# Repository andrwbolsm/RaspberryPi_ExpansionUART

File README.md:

## Context
 
The Raspberry Pi exposes only one hardware UART, which is insufficient when simultaneous communication with multiple devices is required. In this project, each drone in a six-drone swarm uses a dedicated 433 MHz radio transceiver connected over UART. To handle six transceivers from a single Raspberry Pi, a custom expansion board (HAT) was designed using the SC16IS752, natively supported by Linux.
 
A key motivation for moving away from USB was power delivery: the Raspberry Pi's USB ports do not supply enough current to reliably drive multiple radio modules, even through powered hubs. Bypassing USB in favour of direct UART with battery-sourced power resolves this limitation.
 
---
 
## System Architecture
 
```
[ Battery ]
     │
     ├──► [ Voltage Regulator (5V) ] ──► [ SC16IS752 ]
     │                                        │
[ Raspberry Pi ]                       UART A (/dev/ttySC0) ──► Radio transceiver 1
  I²C bus ──────────────────────────►  UART B (/dev/ttySC1) ──► Radio transceiver 2
                                        (stack additional chips for more channels)
```
 
- Power for the SC16IS752 is drawn **directly from the battery** through a regulator, bypassing the Raspberry Pi's USB current limit.
- The I²C bus from the Raspberry Pi controls the chip; Linux automatically exposes each UART as `/dev/ttySC0` and `/dev/ttySC1`.
- Multiple chips can be stacked on the same I²C bus using different A0/A1 addresses, scaling up to 32 UART channels.
 
---
 
## Hardware
 
| Component | Role |
|---|---|
| Raspberry Pi | Main onboard computer (Linux) |
| SC16IS752 | I²C-to-dual-UART bridge chip (2 ch UART + 8 GPIO) |
| 433 MHz radio transceivers | Long-range communication with drones (~400 m through buildings) |
| Voltage regulator | Supplies 5V (≥ 1W) to the chip from the battery |
| Custom HAT PCB | Designed with KiCad; connects directly to the Raspberry Pi GPIO header |
 
The radio modules operate in the **433 MHz band**, each assigned a separate channel to avoid inter-drone interference.
 
---
 
## Repository Structure
 
```
.
├── Code/               # Firmware / communication validation code (C)
├── Projet_Tschema/     # PCB schematic and layout files (KiCad)
└── README.md
```
 
---
 
## Setup
 
### 1. Enable I²C on the Raspberry Pi
 
```bash
sudo raspi-config
# Navigate to: Interfacing Options → I2C → Yes
```
 
### 2. Register the SC16IS752 kernel driver
 
Append to `/boot/config.txt`:
 
```
dtoverlay=sc16is752-i2c,int_pin=24,addr=0x48
# addr changes according to A0/A1 jumper setting — default is 0x48
```
 
Then reboot:
 
```bash
sudo reboot
```
 
### 3. Verify UART devices are exposed
 
```bash
ls /dev/ttySC*
# Expected: /dev/ttySC0  /dev/ttySC1
```
 
---
 
## PCB Design
 
The expansion board is designed in **KiCad** (files in `Projet_Tschema/`). It plugs onto the Raspberry Pi GPIO header and provides:
 
- I²C connection to the SC16IS752
- Battery-sourced regulated 5V power rail for the chip
- UART connectors for each radio transceiver
   
---
 
## Software
 
The firmware (`Code/`, C) handles:
 
1. **UART validation** — confirms Linux correctly enumerates `/dev/ttySC0` and `/dev/ttySC1` after the HAT is mounted.
2. **Communication protocol** — data exchange with each radio transceiver over its dedicated UART channel.
 
---

## Validation Steps
 
1. Mount the HAT and power the SC16IS752 from the battery rail.
2. Confirm UART devices appear: `ls /dev/ttySC*`
3. Run the communication test to validate send/receive on one channel.
 
---
 
## Status
 
> Active development — PCB validation and multi-channel firmware in progress.

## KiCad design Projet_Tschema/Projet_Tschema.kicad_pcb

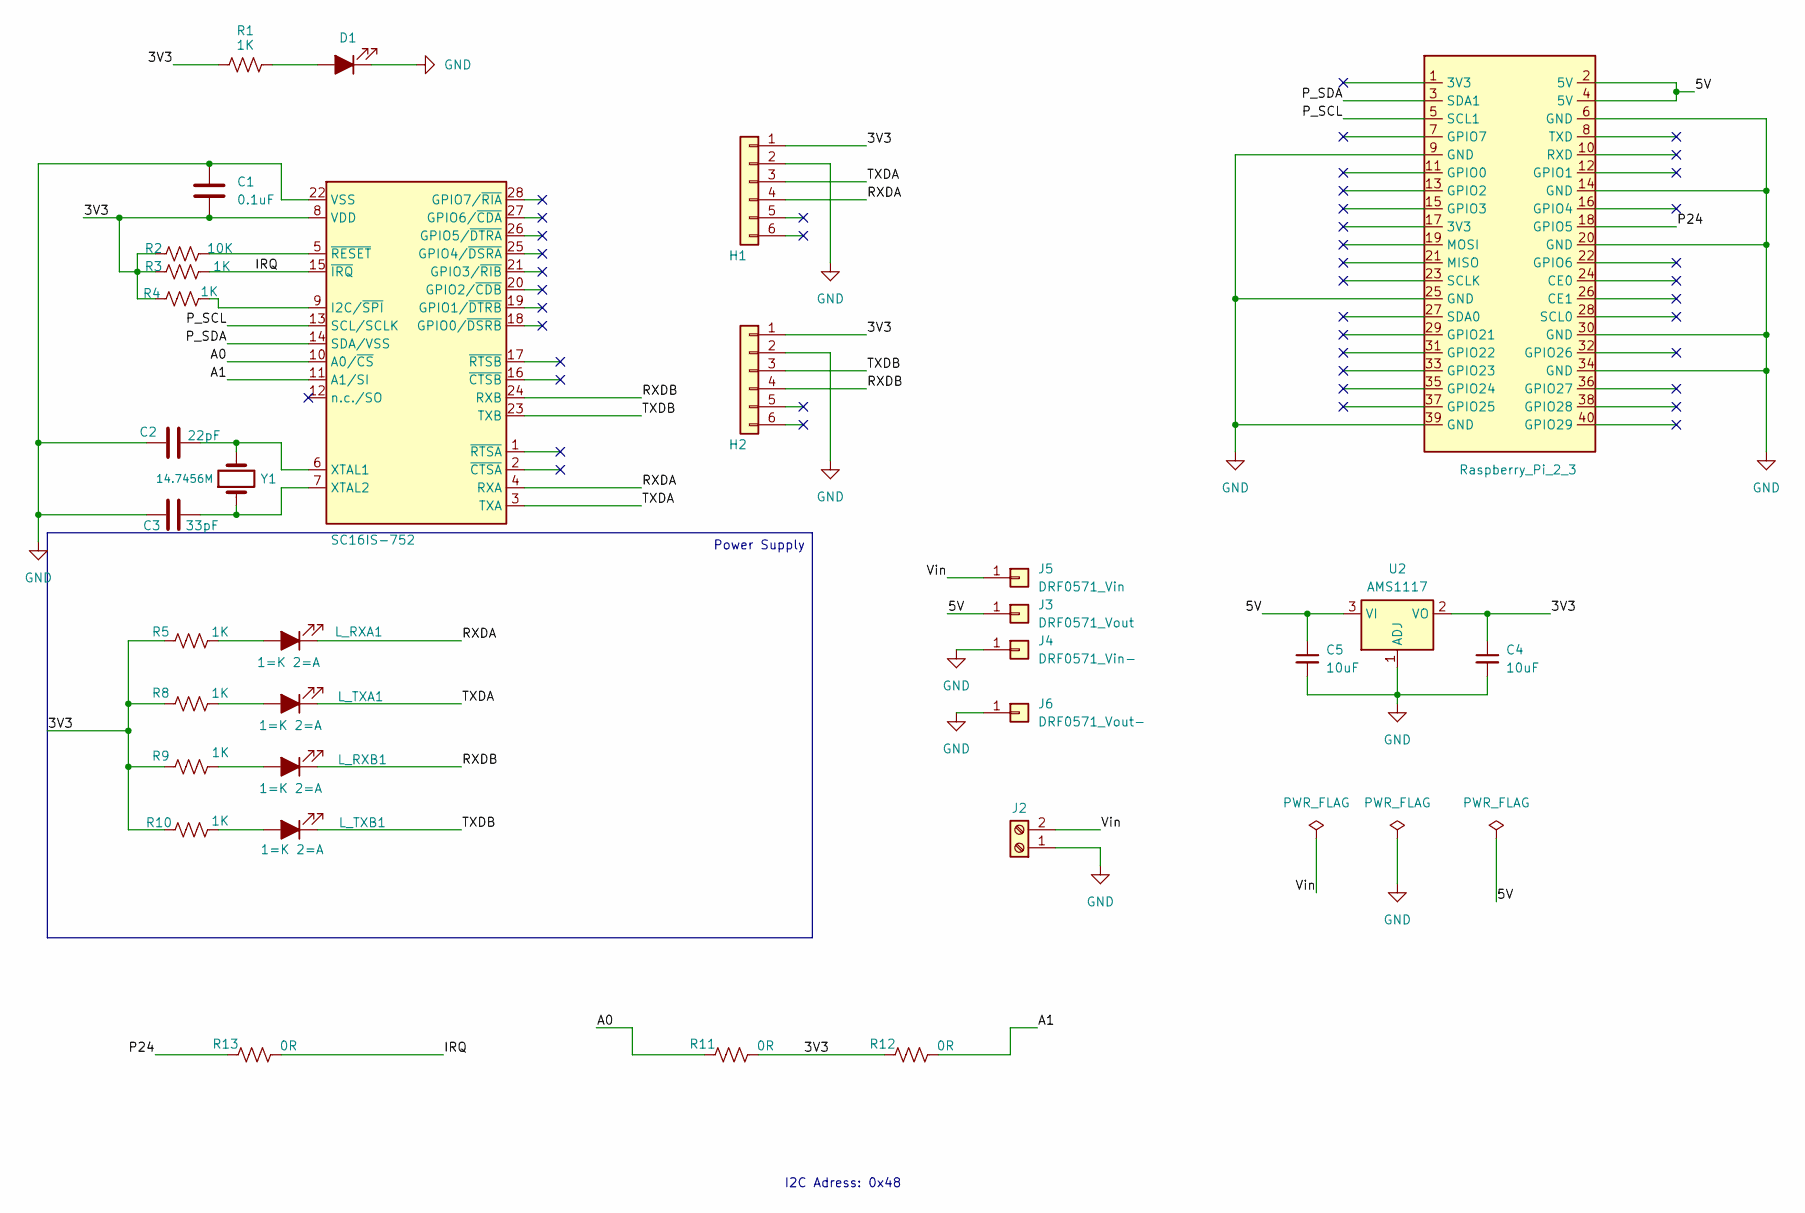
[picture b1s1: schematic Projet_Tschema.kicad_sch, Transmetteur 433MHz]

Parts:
C1: 0.1uF; C_0805_2012Metric
C2: 22pF; C_0805_2012Metric
C3: 33pF; C_0805_2012Metric
C4, C5: 10uF; C_0805_2012Metric
D1: LED_Filled; LED_0805_2012Metric
H1, H2: Conn_01x06; JST_GH_SM06B-GHS-TB_1x06-1MP_P1.25mm_Horizontal
J1: Raspberry_Pi_2_3; PinHeader_2x20_P2.54mm_Vertical
J2: Screw_Terminal_01x02; PinHeader_1x02_P2.54mm_Vertical
J3: DRF0571_Vout; PinHeader_1x01_P2.54mm_Vertical
J4: DRF0571_Vin-; PinHeader_1x01_P2.54mm_Vertical
J5: DRF0571_Vin; PinHeader_1x01_P2.54mm_Vertical
J6: DRF0571_Vout-; PinHeader_1x01_P2.54mm_Vertical
L_RXA1: LED_Filled; R_0805_2012Metric
L_RXB1: LED_Filled; R_0805_2012Metric
L_TXA1: LED_Filled; R_0805_2012Metric
L_TXB1: LED_Filled; R_0805_2012Metric
R1, R3, R4, R5, R8, R9, R10: 1K; R_0805_2012Metric
R2: 10K; R_0805_2012Metric
R11, R12, R13: 0R; R_0805_2012Metric
U1: SC16IS-752; TSSOP-28_4.4x9.7mm_P0.65mm
U2: AMS1117; SOT-223-3_TabPin2
Y1: 14.7456M; Crystal_HC52-U_Vertical

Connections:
/3V3: C1.2, C4.1, H1.1, H2.1, R1.1, R2.1, R3.1, R4.1, R5.1, R8.1, R9.1, R10.1, R11.2, R12.1, U1.8 (VDD), U2.2 (VO)
/5V: C5.1, J1.2 (5V), J1.4 (5V), J3.1, U2.3 (VI)
/&lt;NO NET&gt;: J1.27 (SDA0)
/A0: R11.1, U1.10 (A0/~CS)
/A1: R12.2, U1.11 (A1/SI)
/IRQ: R3.2, R13.2, U1.15 (~IRQ)
/P24: J1.18 (GPIO5), R13.1
/P_SCL: J1.5 (SCL1), U1.13 (SCL/SCLK)
/P_SDA: J1.3 (SDA1), U1.14 (SDA/VSS)
/RXDA: H1.4, L_RXA1.1 (K), U1.4 (RXA)
/RXDB: H2.4, L_RXB1.1 (K), U1.24 (RXB)
/TXDA: H1.3, L_TXA1.1 (K), U1.3 (TXA)
/TXDB: H2.3, L_TXB1.1 (K), U1.23 (TXB)
/Vin: J2.2, J5.1
GND: C1.1, C2.2, C3.2, C4.2, C5.2, D1.1 (K), H1.2, H2.2, J1.6 (GND), J1.9 (GND), J1.14 (GND), J1.20 (GND), J1.25 (GND), J1.30 (GND), J1.34 (GND), J1.39 (GND), J2.1, J4.1, J6.1, U1.22 (VSS), U2.1 (ADJ)
unnamed: D1.2 (A), R1.2
unnamed: L_RXA1.2 (A), R5.2
unnamed: L_RXB1.2 (A), R9.2
unnamed: L_TXA1.2 (A), R8.2
unnamed: L_TXB1.2 (A), R10.2
unnamed: R4.2, U1.9 (I2C/~SPI)
unnamed: C2.1, U1.6 (XTAL1), Y1.2
unnamed: C3.1, U1.7 (XTAL2), Y1.1
unnamed: R2.2, U1.5 (~RESET)

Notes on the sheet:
I2C Adress: 0x48
Power Supply

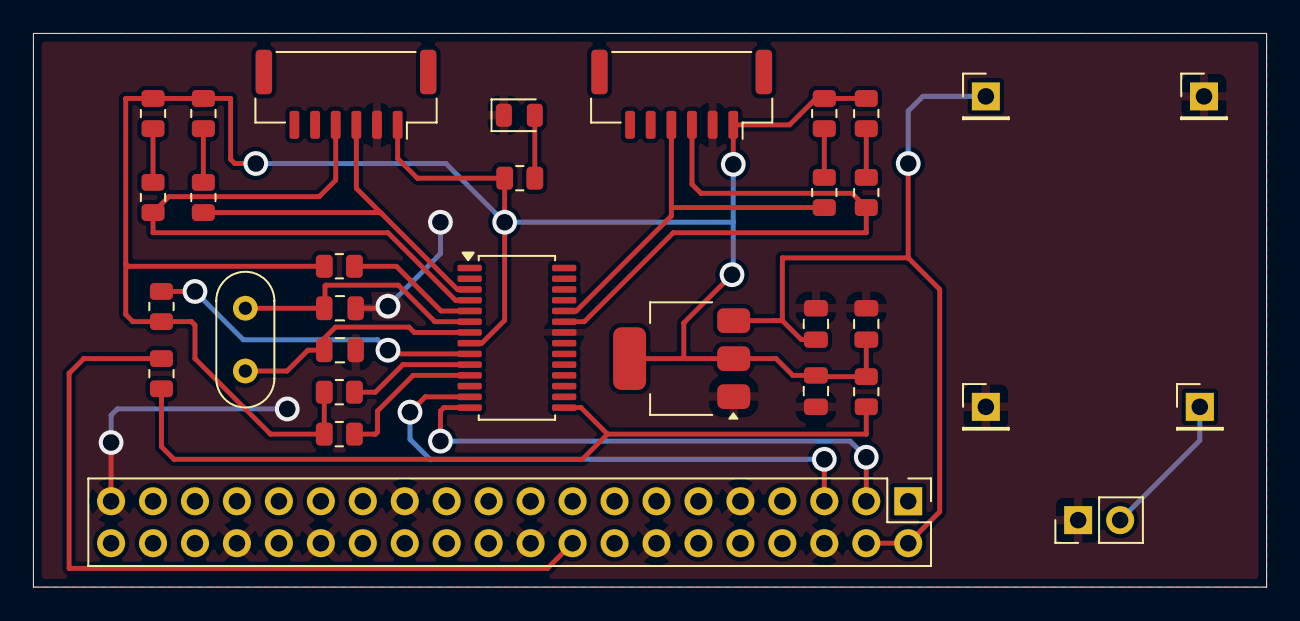
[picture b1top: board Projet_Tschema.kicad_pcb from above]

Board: 2 copper layers, 74.7 x 33.5 mm, 32 parts (0 on the bottom side), 23 nets.

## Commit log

2026-02-27 Premier commit : initialisation du projet
2026-03-12 first version finished
2026-03-13 adding software
2026-03-17 routes updated
2026-03-19 Final adjustments for gerber generation
